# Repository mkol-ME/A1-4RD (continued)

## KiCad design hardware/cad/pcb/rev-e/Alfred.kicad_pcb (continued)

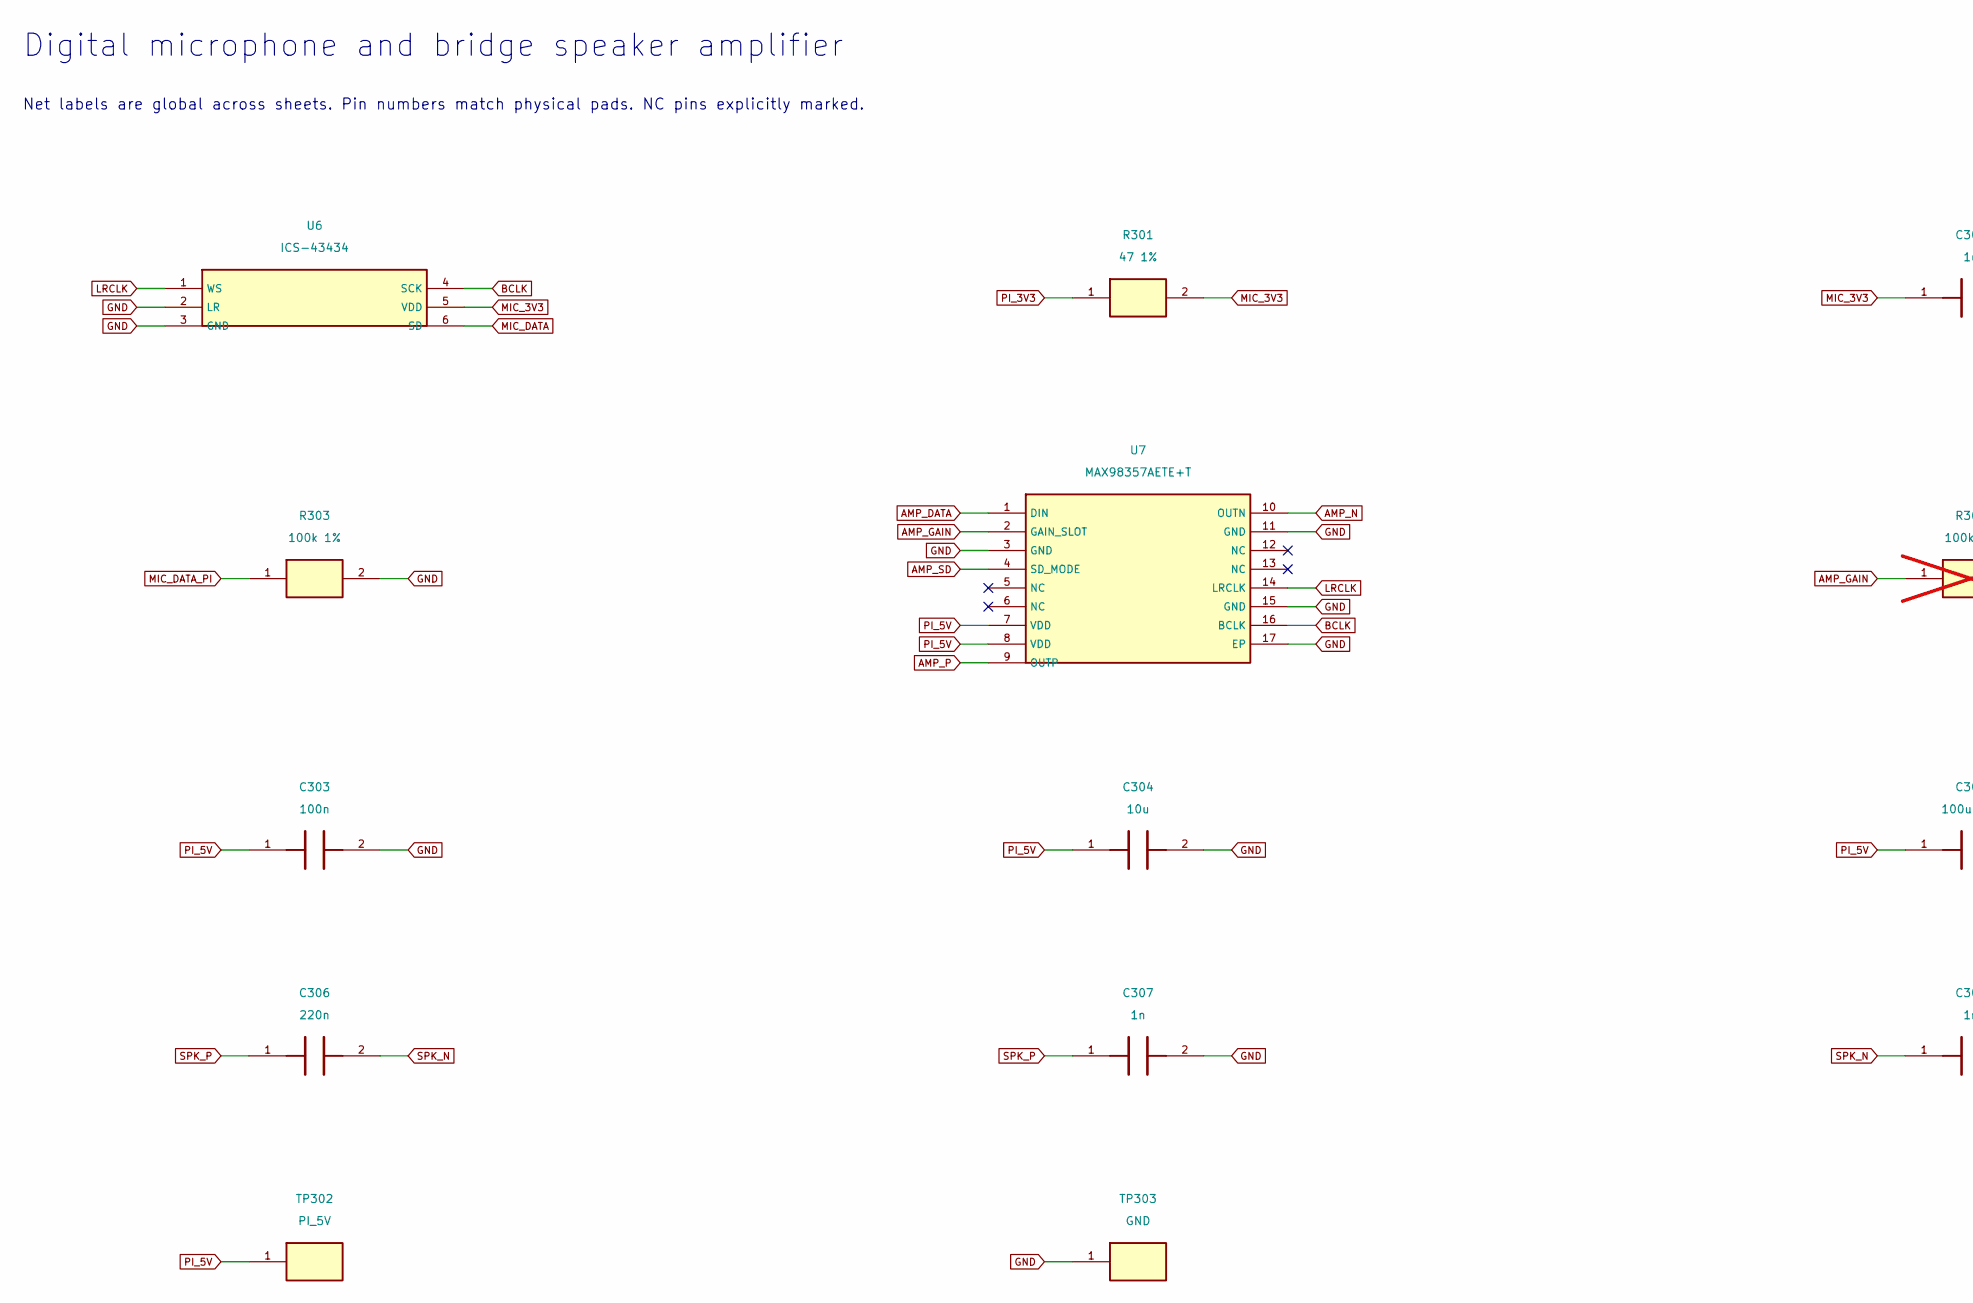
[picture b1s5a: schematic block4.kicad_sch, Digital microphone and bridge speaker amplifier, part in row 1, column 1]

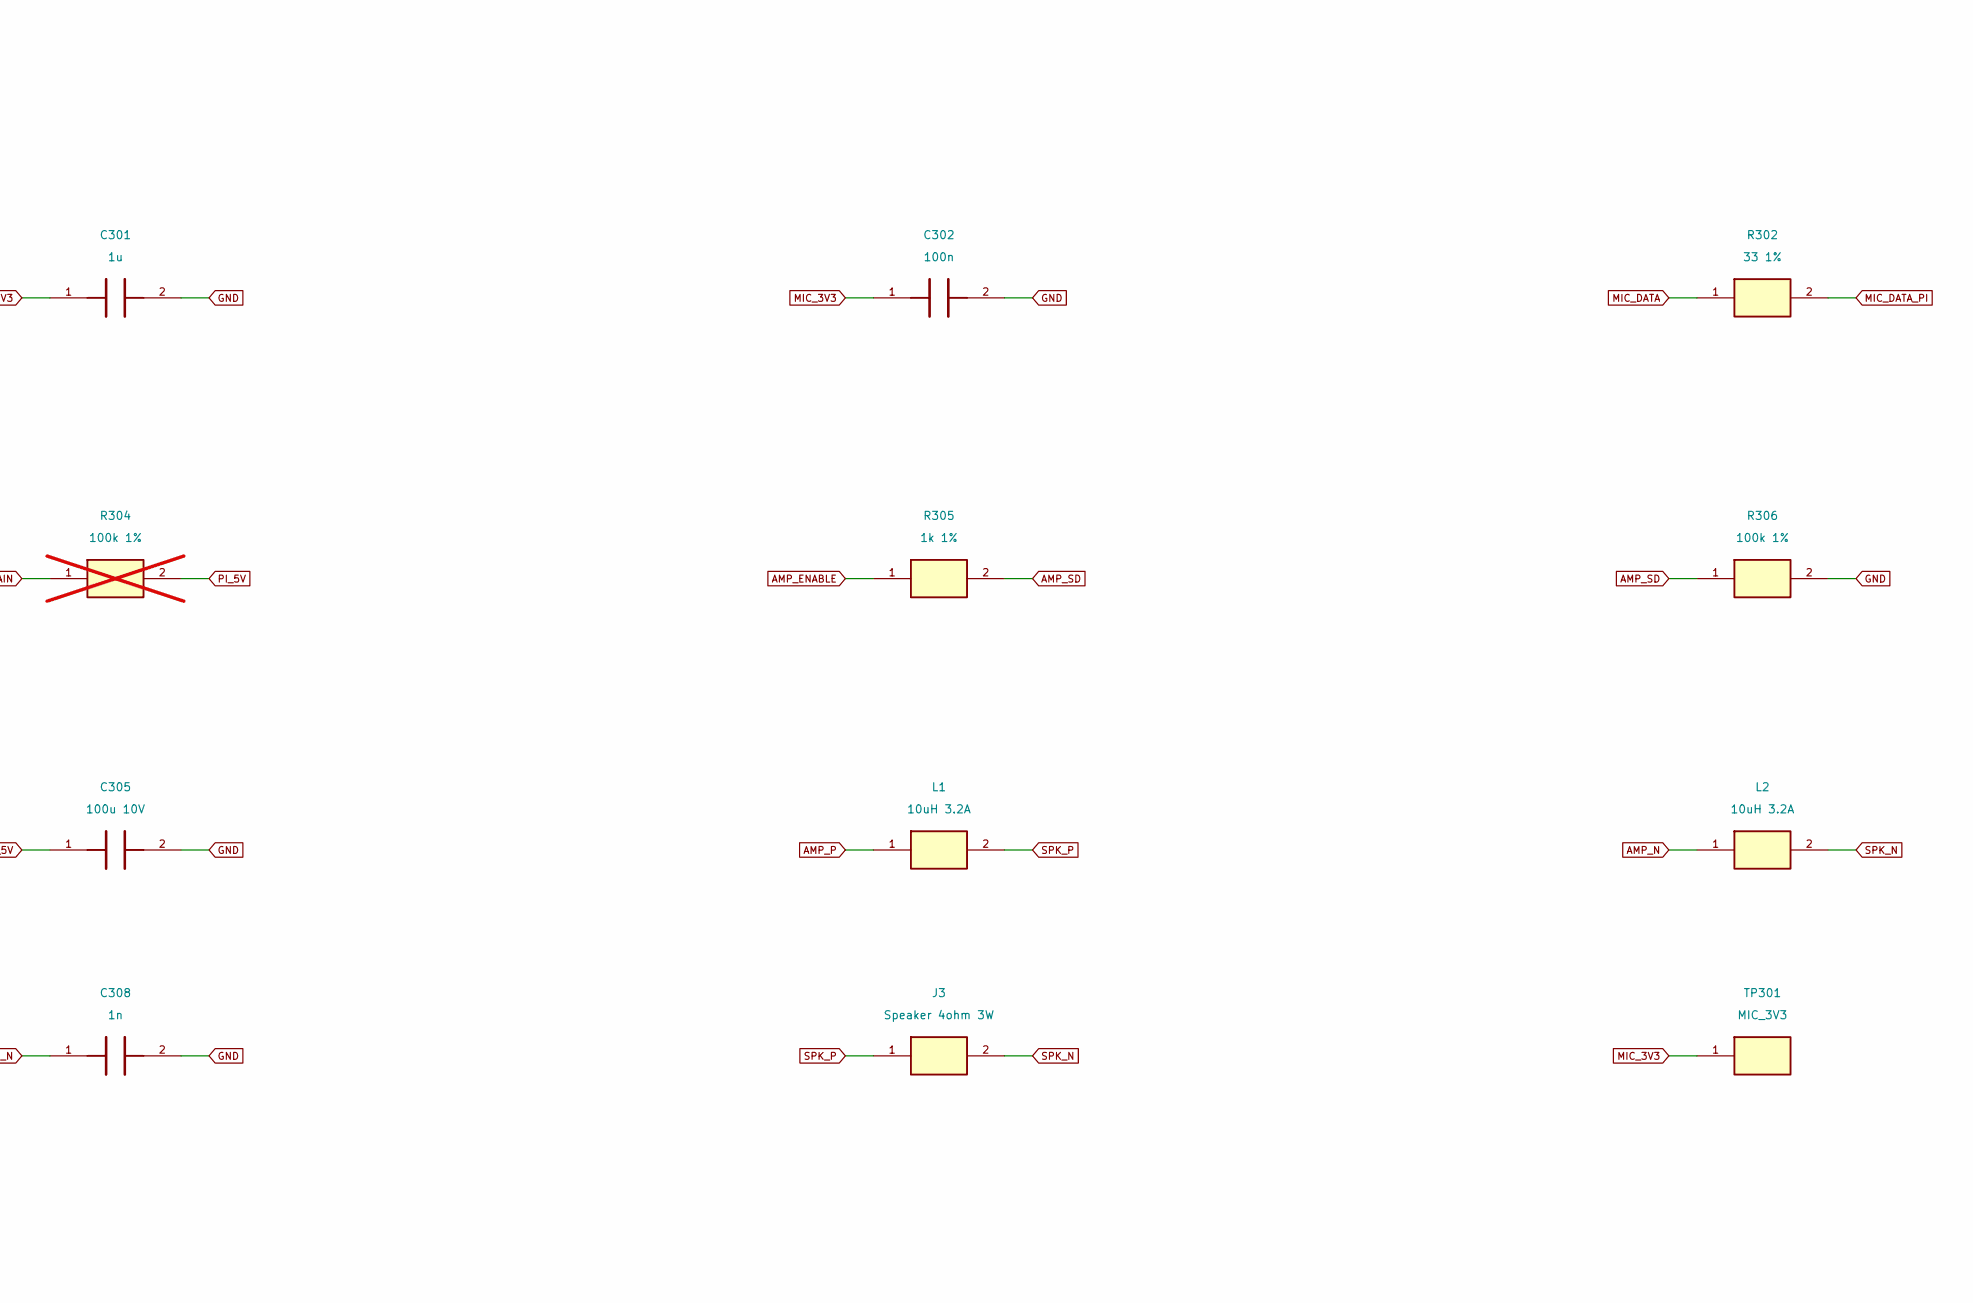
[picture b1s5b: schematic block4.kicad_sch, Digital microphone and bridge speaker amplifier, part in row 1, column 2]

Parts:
C301: 1u; C_0805_2012Metric; MPN C0805C105K5RACTU
C302, C303: 100n; C_0805_2012Metric; MPN C0805C104K5RACTU
C304: 10u; C_1206_3216Metric; MPN C1206C106K4RACTU
C305: 100u 10V; CP_Radial_D5.0mm_P2.00mm; MPN EEU-FR1A101
C306: 220n; C_0805_2012Metric; MPN C0805C224K5RACTU
C307, C308: 1n; C_0805_2012Metric; MPN C0805C102J5GACTU
J3: Speaker 4ohm 3W; TerminalBlock_TE_282834-2_1x02_P2.54mm_Horizontal; MPN 282834-2
L1, L2: 10uH 3.2A; SRN6045TA_100M; MPN SRN6045TA-100M
R301: 47 1%; R_0805_2012Metric; MPN RC0805FR-0747RL
R302: 33 1%; R_0805_2012Metric; MPN RC0805FR-0733RL
R303, R306: 100k 1%; R_0805_2012Metric; MPN RC0805FR-07100KL
R304: 100k 1%; R_0805_DNP_NoPaste; MPN RC0805FR-07100KL; not fitted
R305: 1k 1%; R_0805_2012Metric; MPN RC0805FR-071KL
TP301: MIC_3V3; TestPoint_Pad_D1.5mm; MPN PCB copper test point
TP302: PI_5V; TestPoint_Pad_D1.5mm; MPN PCB copper test point
TP303: GND; TestPoint_Pad_D1.5mm; MPN PCB copper test point
U6: ICS-43434; InvenSense_ICS-43434-6_3.5x2.65mm; MPN ICS-43434
U7: MAX98357AETE+T; TQFN-16-1EP_3x3mm_P0.5mm_EP1.23x1.23mm; MPN MAX98357AETE+T

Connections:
AMP_DATA: U7.1 (DIN); also elsewhere on the board
AMP_ENABLE: R305.1; also elsewhere on the board
AMP_GAIN: R304.1, U7.2 (GAIN_SLOT)
AMP_N: L2.1, U7.10 (OUTN)
AMP_P: L1.1, U7.9 (OUTP)
AMP_SD: R305.2, R306.1, U7.4 (SD_MODE)
BCLK: U6.4 (SCK), U7.16 (BCLK); also elsewhere on the board
GND: C301.2, C302.2, C303.2, C304.2, C305.2, C307.2, C308.2, R303.2, R306.2, TP303.1, U6.2 (LR), U6.3 (GND), U7.3 (GND), U7.11 (GND), U7.15 (GND), U7.17 (EP); also elsewhere on the board
LRCLK: U6.1 (WS), U7.14 (LRCLK); also elsewhere on the board
MIC_3V3: C301.1, C302.1, R301.2, TP301.1, U6.5 (VDD)
MIC_DATA: R302.1, U6.6 (SD)
MIC_DATA_PI: R302.2, R303.1; also elsewhere on the board
PI_3V3: R301.1; also elsewhere on the board
PI_5V: C303.1, C304.1, C305.1, R304.2, TP302.1, U7.7 (VDD), U7.8 (VDD); also elsewhere on the board
SPK_N: C306.2, C308.1, J3.2, L2.2
SPK_P: C306.1, C307.1, J3.1, L1.2

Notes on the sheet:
Digital microphone and bridge speaker amplifier
Net labels are global across sheets. Pin numbers match physical pads. NC pins explicitly marked.

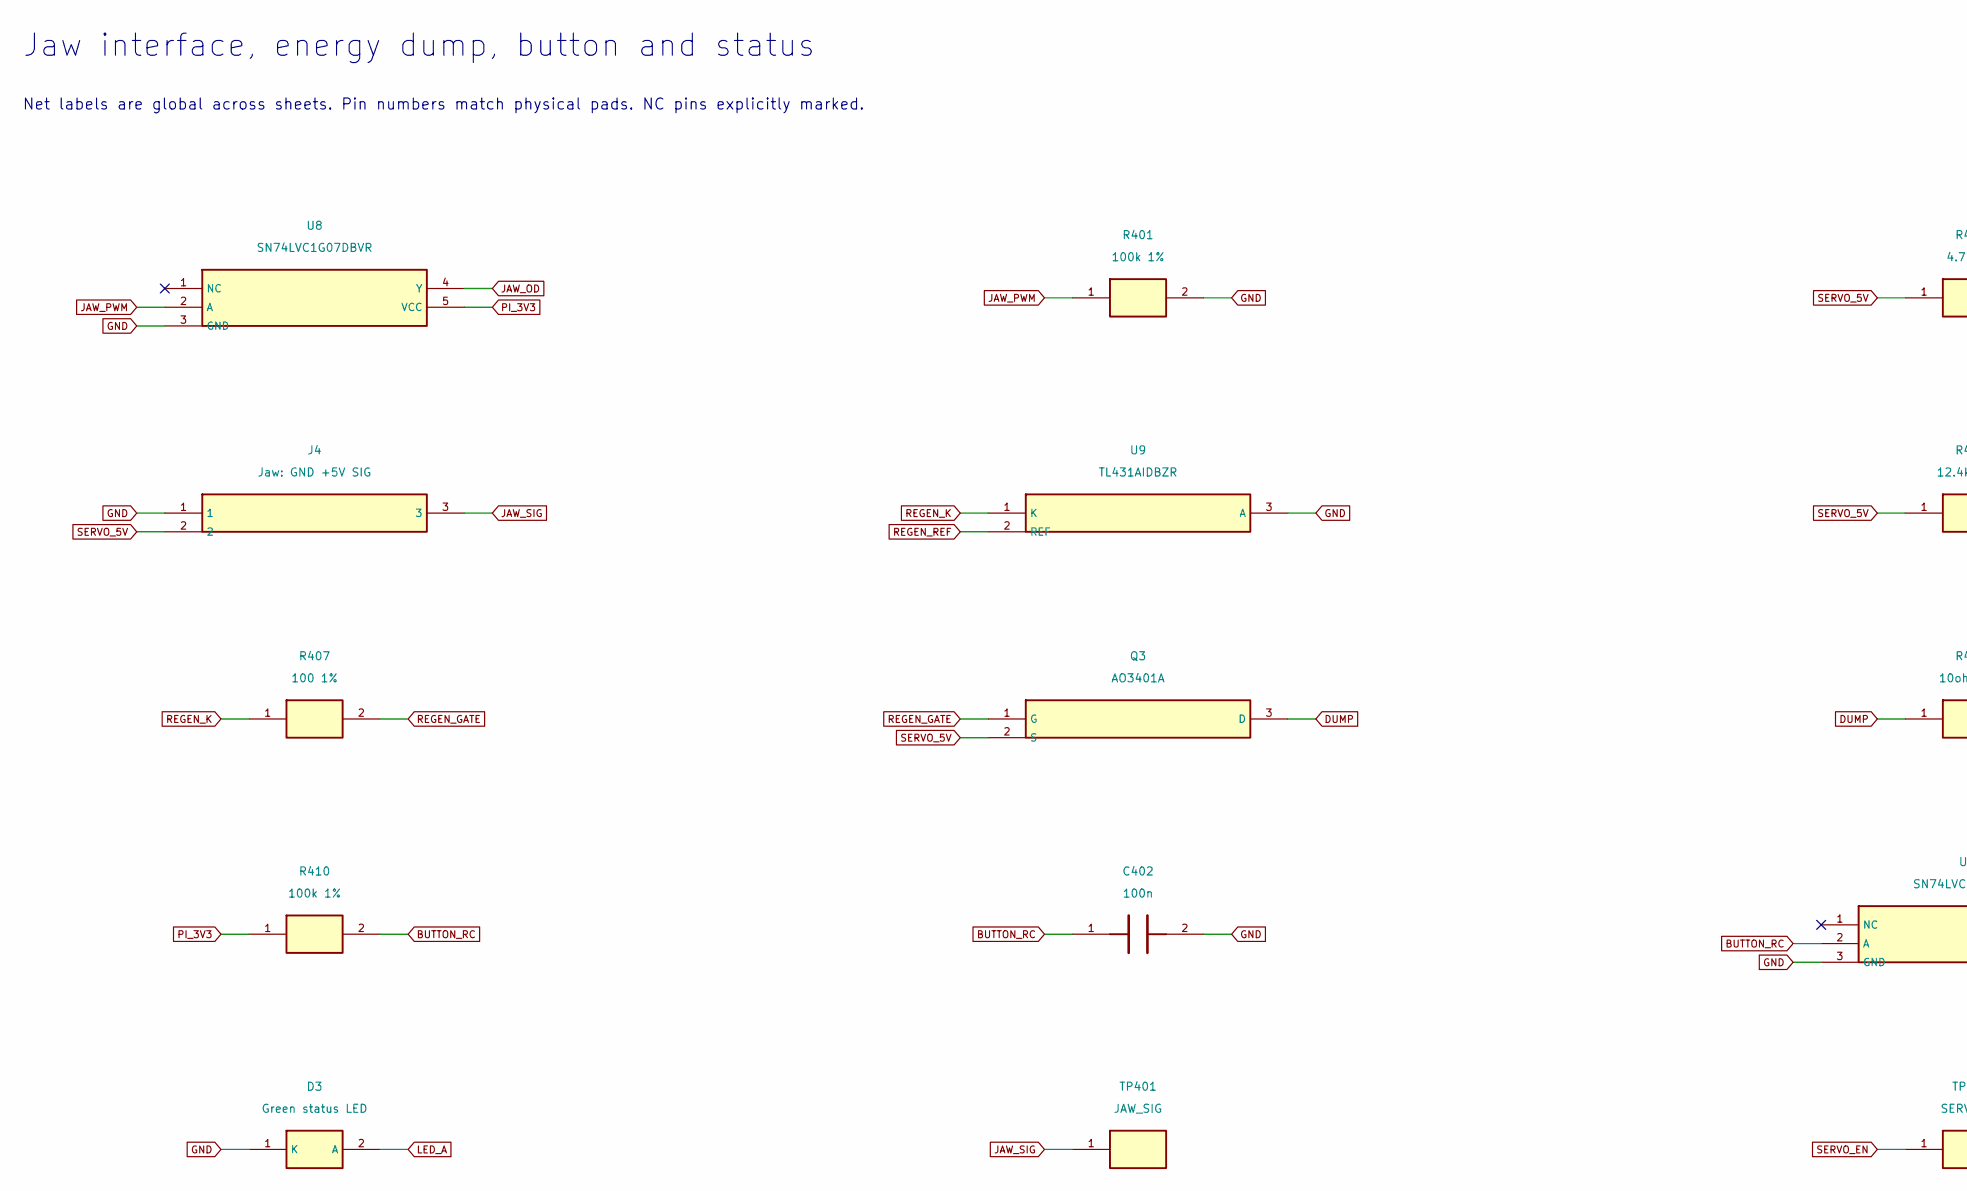
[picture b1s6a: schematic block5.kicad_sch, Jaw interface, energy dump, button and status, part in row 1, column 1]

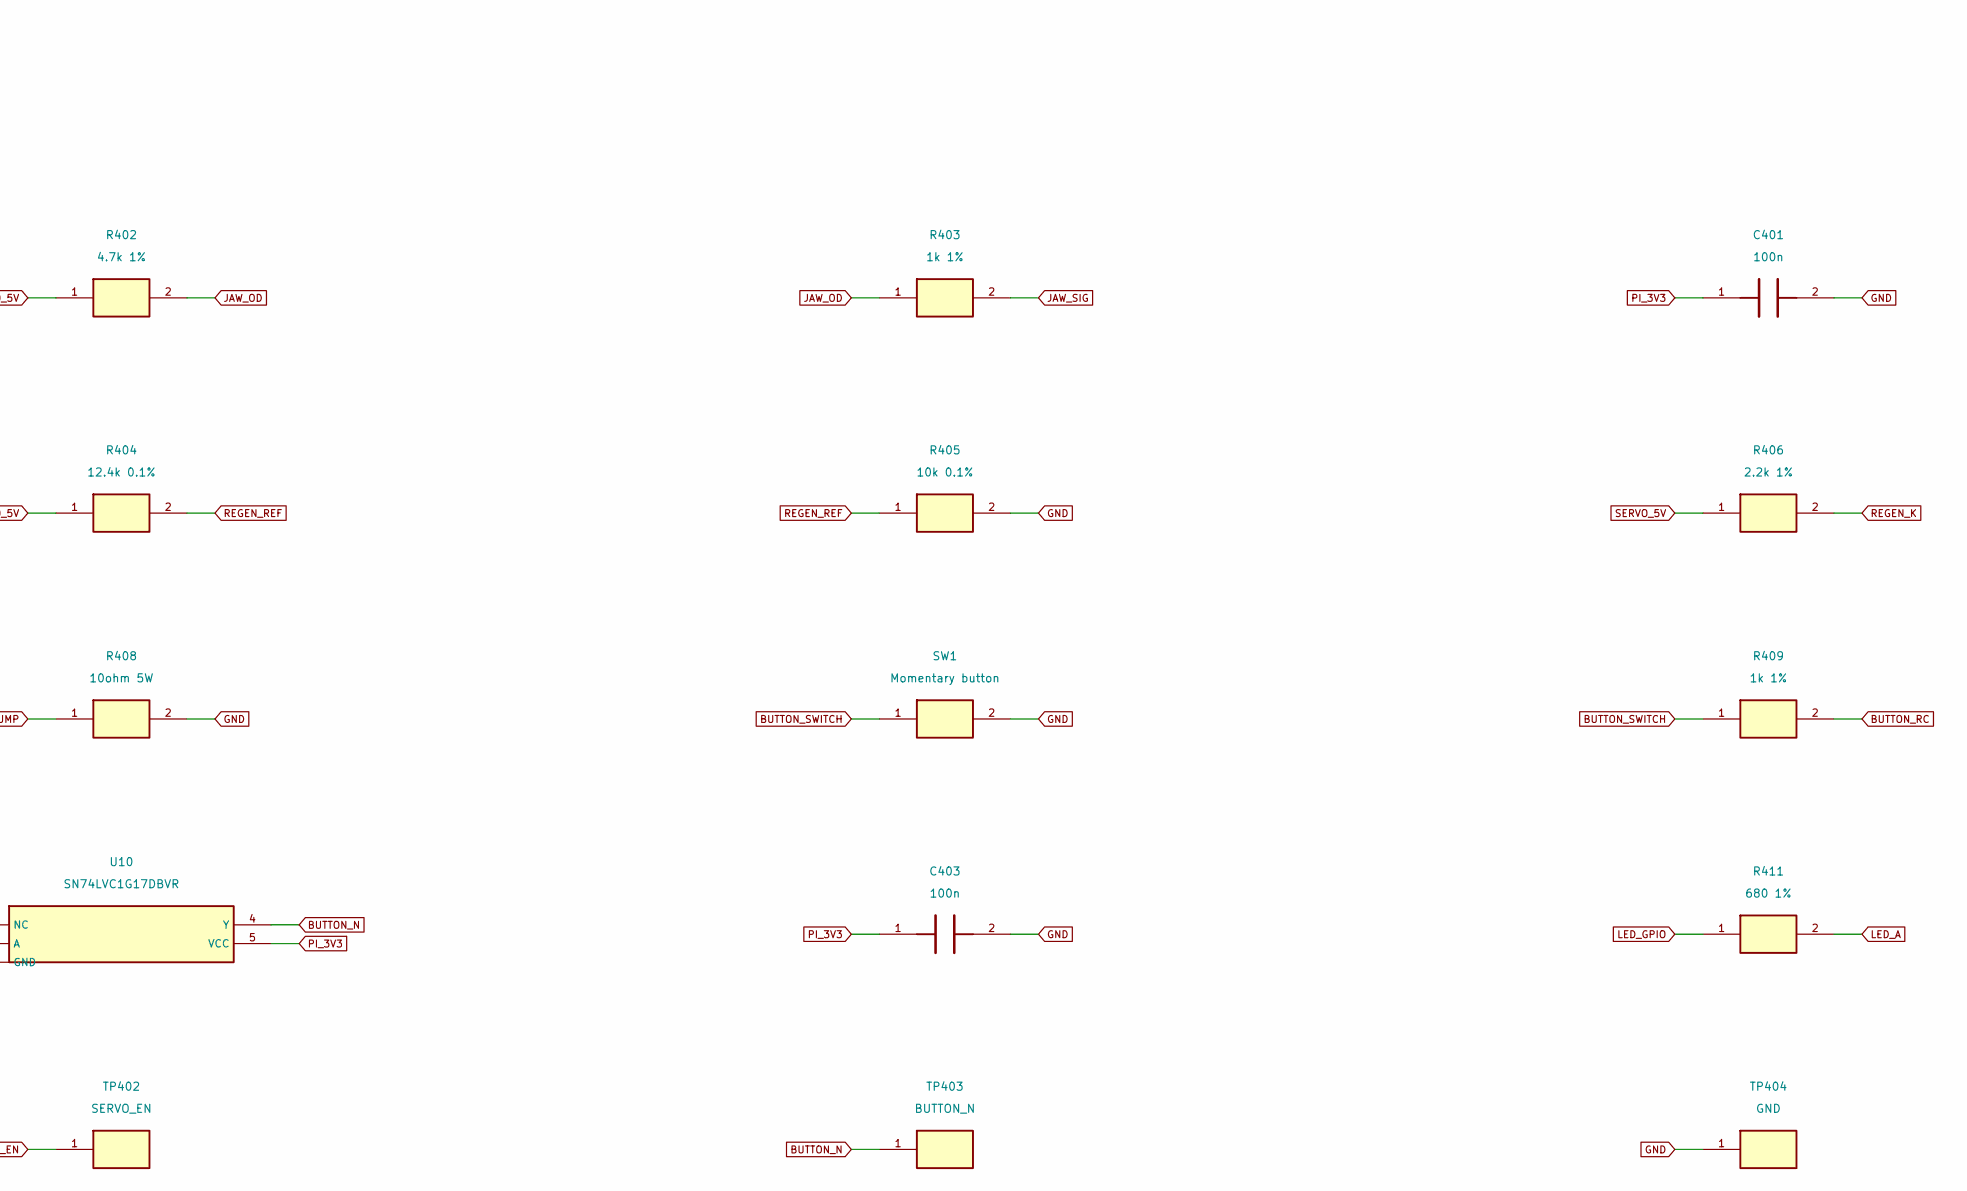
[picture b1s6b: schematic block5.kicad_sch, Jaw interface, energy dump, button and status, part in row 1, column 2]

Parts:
C401, C402, C403: 100n; C_0805_2012Metric; MPN C0805C104K5RACTU
D3: Green status LED; LED_D3.0mm; MPN WP710A10SGC
J4: Jaw: GND +5V SIG; PinHeader_1x03_P2.54mm_Vertical; MPN TSW-103-07-G-S
Q3: AO3401A; SOT-23; MPN AO3401A
R401, R410: 100k 1%; R_0805_2012Metric; MPN RC0805FR-07100KL
R402: 4.7k 1%; R_0805_2012Metric; MPN RC0805FR-074K7L
R403, R409: 1k 1%; R_0805_2012Metric; MPN RC0805FR-071KL
R404: 12.4k 0.1%; R_0805_2012Metric; MPN RT0805BRD0712K4L
R405: 10k 0.1%; R_0805_2012Metric; MPN RT0805BRD0710KL
R406: 2.2k 1%; R_0805_2012Metric; MPN RC0805FR-072K2L
R407: 100 1%; R_0805_2012Metric; MPN RC0805FR-07100RL
R408: 10ohm 5W; R_Axial_Power_L25.0mm_W9.0mm_P30.48mm; MPN SQP500JB-10R
R411: 680 1%; R_0805_2012Metric; MPN RC0805FR-07680RL
SW1: Momentary button; SW_PUSH_6mm_H4.3mm; MPN B3F-1000
TP401: JAW_SIG; TestPoint_Pad_D1.5mm; MPN PCB copper test point
TP402: SERVO_EN; TestPoint_Pad_D1.5mm; MPN PCB copper test point
TP403: BUTTON_N; TestPoint_Pad_D1.5mm; MPN PCB copper test point
TP404: GND; TestPoint_Pad_D1.5mm; MPN PCB copper test point
U8: SN74LVC1G07DBVR; SOT-23-5; MPN SN74LVC1G07DBVR
U9: TL431AIDBZR; SOT-23; MPN TL431AIDBZR
U10: SN74LVC1G17DBVR; SOT-23-5; MPN SN74LVC1G17DBVR

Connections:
BUTTON_N: TP403.1, U10.4 (Y); also elsewhere on the board
BUTTON_RC: C402.1, R409.2, R410.2, U10.2 (A)
BUTTON_SWITCH: R409.1, SW1.1
DUMP: Q3.3 (D), R408.1
GND: C401.2, C402.2, C403.2, D3.1 (K), J4.1, R401.2, R405.2, R408.2, SW1.2, TP404.1, U8.3 (GND), U9.3 (A), U10.3 (GND); also elsewhere on the board
JAW_OD: R402.2, R403.1, U8.4 (Y)
JAW_PWM: R401.1, U8.2 (A); also elsewhere on the board
JAW_SIG: J4.3, R403.2, TP401.1
LED_A: D3.2 (A), R411.2
LED_GPIO: R411.1; also elsewhere on the board
PI_3V3: C401.1, C403.1, R410.1, U8.5 (VCC), U10.5 (VCC); also elsewhere on the board
REGEN_GATE: Q3.1 (G), R407.2
REGEN_K: R406.2, R407.1, U9.1 (K)
REGEN_REF: R404.2, R405.1, U9.2 (REF)
SERVO_5V: J4.2, Q3.2 (S), R402.1, R404.1, R406.1; also elsewhere on the board
SERVO_EN: TP402.1; also elsewhere on the board

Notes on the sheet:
Jaw interface, energy dump, button and status
Net labels are global across sheets. Pin numbers match physical pads. NC pins explicitly marked.

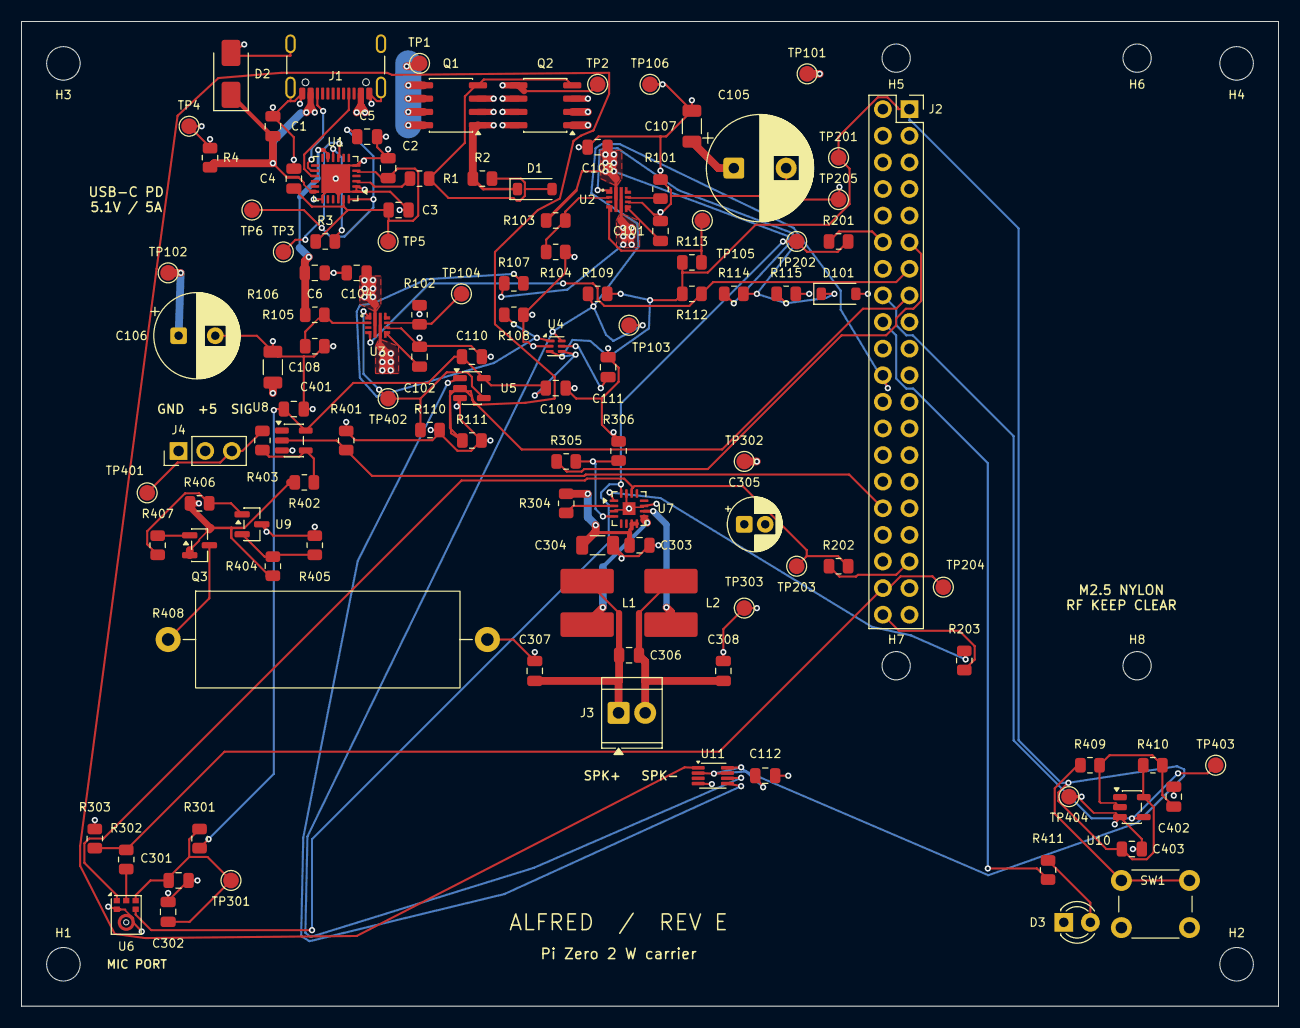
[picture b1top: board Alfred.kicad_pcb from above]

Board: 4 copper layers, 120.0 x 94.0 mm, 125 parts (0 on the bottom side), 58 nets.

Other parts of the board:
H1, H2, H3, H4: MountingHole_3.2mm_M3
H5, H6, H7, H8: MountingHole_2.7mm_M2.5

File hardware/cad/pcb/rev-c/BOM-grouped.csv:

References fitted,Quantity fitted per board,Lean purchase quantity for ONE board,Optional purchase with small-passive spares,MPN,Value,Footprint,Unit USD allowance - NOT QUOTE,Lean extended USD allowance,Price evidence
J3,1,1,1,282834-2,Speaker 4ohm 3W,TerminalBlock_TE-Connectivity:TerminalBlock_TE_282834-2_1x02_P2.54mm_Horizontal,0.8,0.8,Inherited allowance; refresh supplier cart
Q3,1,1,1,AO3401A,AO3401A,Package_TO_SOT_SMD:SOT-23,0.25,0.25,Inherited allowance; refresh supplier cart
SW1,1,1,1,B3F-1000,Momentary button,Button_Switch_THT:SW_PUSH_6mm_H4.3mm,0.3,0.3,Inherited allowance; refresh supplier cart
D1,1,1,1,BZT52C10-7-F,10V gate zener,Diode_SMD:D_SOD-123,0.12,0.12,Inherited allowance; refresh supplier cart
"C111, C307, C308",3,3,5,C0805C102J5GACTU,1n,Capacitor_SMD:C_0805_2012Metric,0.15,0.45,Inherited allowance; refresh supplier cart
"C3, C4, C103, C104, C109, C110, C302, C303, C401, C402, C403",11,11,13,C0805C104K5RACTU,100n,Capacitor_SMD:C_0805_2012Metric,0.15,1.65,Inherited allowance; refresh supplier cart
"C1, C2, C5, C6, C301",5,5,7,C0805C105K5RACTU,1u,Capacitor_SMD:C_0805_2012Metric,0.15,0.75,Inherited allowance; refresh supplier cart
C306,1,1,3,C0805C224K5RACTU,220n,Capacitor_SMD:C_0805_2012Metric,0.15,0.15,Inherited allowance; refresh supplier cart
"C101, C102",2,2,4,C0805C472J5GACTU,4.7n,Capacitor_SMD:C_0805_2012Metric,0.15,0.3,Inherited allowance; refresh supplier cart
"C107, C108, C304",3,3,5,C1206C106K4RACTU,10u,Capacitor_SMD:C_1206_3216Metric,0.15,0.45,Inherited allowance; refresh supplier cart
U1,1,1,1,CYPD3177-24LQXQ,CYPD3177-24LQXQ,Package_DFN_QFN:QFN-24-1EP_4x4mm_P0.5mm_EP2.75x2.75mm,3.5,3.5,Inherited allowance; refresh supplier cart
C305,1,1,1,EEU-FR1A101,100u 10V,Capacitor_THT:CP_Radial_D5.0mm_P2.00mm,0.35,0.35,Inherited allowance; refresh supplier cart
C106,1,1,1,EEU-FR1A102L,1000u 10V,Capacitor_THT:CP_Radial_D8.0mm_P3.50mm,0.85,0.85,Inherited allowance; refresh supplier cart
C105,1,1,1,EEU-FR1A222L,2200u 10V,Capacitor_THT:CP_Radial_D10.0mm_P5.00mm,1.3,1.3,Inherited allowance; refresh supplier cart
"Q1, Q2",2,2,2,FDS6673BZ,FDS6673BZ,Package_SO:SO-8_3.9x4.9mm_P1.27mm,1.76,3.52,"DigiKey indexed substitute listing: $1.76, 4781 in stock, checked 2026-09-10; not reserved"
U6,1,1,1,ICS-43434,ICS-43434,Sensor_Audio:InvenSense_ICS-43434-6_3.5x2.65mm,4.2,4.2,Inherited allowance; refresh supplier cart
U7,1,1,1,MAX98357AETE+T,MAX98357AETE+T,Package_DFN_QFN:TQFN-16-1EP_3x3mm_P0.5mm_EP1.23x1.23mm,4.08,4.08,Inherited allowance; refresh supplier cart
D101,1,1,1,MMSZ5V1T1G,5.1V EN clamp,Diode_SMD:D_SOD-123,0.17,0.17,"DigiKey indexed substitute listing: $0.17, 101196 in stock, checked 2026-09-10; not reserved"
"R2, R110, R111, R303, R306, R401, R410",7,7,9,RC0805FR-07100KL,100k 1%,Resistor_SMD:R_0805_2012Metric,0.05,0.35,Inherited allowance; refresh supplier cart
R407,1,1,3,RC0805FR-07100RL,100 1%,Resistor_SMD:R_0805_2012Metric,0.05,0.05,Inherited allowance; refresh supplier cart
"R4, R112, R113, R114, R115",5,5,7,RC0805FR-0710KL,10k 1%,Resistor_SMD:R_0805_2012Metric,0.05,0.25,Inherited allowance; refresh supplier cart
"R1, R305, R403, R409",4,4,6,RC0805FR-071KL,1k 1%,Resistor_SMD:R_0805_2012Metric,0.05,0.2,Inherited allowance; refresh supplier cart
R406,1,1,3,RC0805FR-072K2L,2.2k 1%,Resistor_SMD:R_0805_2012Metric,0.05,0.05,Inherited allowance; refresh supplier cart
R109,1,1,3,RC0805FR-072M2L,2.2M 1%,Resistor_SMD:R_0805_2012Metric,0.05,0.05,Inherited allowance; refresh supplier cart
"R201, R202, R203, R302",4,4,6,RC0805FR-0733RL,33 1%,Resistor_SMD:R_0805_2012Metric,0.05,0.2,Inherited allowance; refresh supplier cart
R301,1,1,3,RC0805FR-0747RL,47 1%,Resistor_SMD:R_0805_2012Metric,0.05,0.05,Inherited allowance; refresh supplier cart
R3,1,1,3,RC0805FR-0749K9L,49.9k 1%,Resistor_SMD:R_0805_2012Metric,0.05,0.05,Inherited allowance; refresh supplier cart
R402,1,1,3,RC0805FR-074K7L,4.7k 1%,Resistor_SMD:R_0805_2012Metric,0.05,0.05,Inherited allowance; refresh supplier cart
R411,1,1,3,RC0805FR-07680RL,680 1%,Resistor_SMD:R_0805_2012Metric,0.05,0.05,Inherited allowance; refresh supplier cart
"R104, R106, R108, R405",4,4,6,RT0805BRD0710KL,10k 0.1%,Resistor_SMD:R_0805_2012Metric,0.18,0.72,Inherited allowance; refresh supplier cart
R404,1,1,3,RT0805BRD0712K4L,12.4k 0.1%,Resistor_SMD:R_0805_2012Metric,0.18,0.18,Inherited allowance; refresh supplier cart
R101,1,1,3,RT0805BRD071KL,1k 0.1%,Resistor_SMD:R_0805_2012Metric,0.18,0.18,Inherited allowance; refresh supplier cart
R107,1,1,3,RT0805BRD0729K8L,29.8k 0.1%,Resistor_SMD:R_0805_2012Metric,0.18,0.18,Inherited allowance; refresh supplier cart
"R103, R105",2,2,4,RT0805BRD0734KL,34.0k 0.1%,Resistor_SMD:R_0805_2012Metric,0.18,0.36,Inherited allowance; refresh supplier cart
R102,1,1,3,RT0805BRD073K32L,3.32k 0.1%,Resistor_SMD:R_0805_2012Metric,0.18,0.18,Inherited allowance; refresh supplier cart
D2,1,1,1,SMAJ15A-13-F,15V transient suppressor,Diode_SMD:D_SMA,0.45,0.45,Inherited allowance; refresh supplier cart
U8,1,1,1,SN74LVC1G07DBVR,SN74LVC1G07DBVR,Package_TO_SOT_SMD:SOT-23-5,0.35,0.35,Inherited allowance; refresh supplier cart
U5,1,1,1,SN74LVC1G08DBVR,SN74LVC1G08DBVR,Package_TO_SOT_SMD:SOT-23-5,0.35,0.35,Inherited allowance; refresh supplier cart
U10,1,1,1,SN74LVC1G17DBVR,SN74LVC1G17DBVR,Package_TO_SOT_SMD:SOT-23-5,0.4,0.4,Inherited allowance; refresh supplier cart
R408,1,1,1,SQP500JB-10R,10ohm 5W,Resistor_THT:R_Axial_Power_L25.0mm_W9.0mm_P30.48mm,0.6,0.6,Inherited allowance; refresh supplier cart
"L1, L2",2,2,2,SRN6045TA-100M,10uH 3.2A,Alfred:SRN6045TA_100M,0.75,1.5,Inherited allowance; refresh supplier cart
J2,1,1,1,SSW-120-01-G-D,Pi Zero 2 W carrier socket,Connector_PinSocket_2.54mm:PinSocket_2x20_P2.54mm_Vertical,4.5,4.5,Inherited allowance; refresh supplier cart
U9,1,1,1,TL431AIDBZR,TL431AIDBZR,Package_TO_SOT_SMD:SOT-23,0.4,0.4,Inherited allowance; refresh supplier cart
U4,1,1,1,TLV3012BIDBVR,TLV3012BIDBVR,Package_TO_SOT_SMD:SOT-23-6,2.78,2.78,Inherited allowance; refresh supplier cart
"U2, U3",2,2,2,TPS259470LRPWR,TPS259470LRPWR,Alfred:TI_RPW0010A,1.72,3.44,Inherited allowance; refresh supplier cart
J4,1,1,1,TSW-103-07-G-S,Jaw: GND +5V SIG,Connector_PinHeader_2.54mm:PinHeader_1x03_P2.54mm_Vertical,0.45,0.45,Inherited allowance; refresh supplier cart
J1,1,1,1,USB4105-GF-A,USB-C 5V/5A PD,Connector_USB:USB_C_Receptacle_GCT_USB4105-xx-A_16P_TopMnt_Horizontal,1.2,1.2,Inherited allowance; refresh supplier cart
D3,1,1,1,WP710A10SGC,Green status LED,LED_THT:LED_D3.0mm,0.3,0.3,Inherited allowance; refresh supplier cart

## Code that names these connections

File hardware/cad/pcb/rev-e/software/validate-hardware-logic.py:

from pathlib import Path
from itertools import product
import json
O=Path(__file__).resolve().parent.parent;by={a['ref']:a for a in json.loads((O/'design-data.json').read_text())}
assert by['U4']['pins']=={'1':'UV_SENSE','2':'GND','3':'PI_3V3','4':'PI_3V3','5':'UV_DELAY','6':'SUPPLY_OK'}
assert by['U11']['pins']=={'1':'SERVO_REQUEST','2':'PI_3V3','3':None,'4':'GND','5':'SERVO_ARMED','6':'SUPPLY_OK','7':'PI_3V3','8':'PI_3V3'}
assert by['U5']['pins']['1']=='SERVO_ARMED' and by['U5']['pins']['2']=='SERVO_REQUEST'
# Exhaust all eight-event binary request/supply-good sequences; start with reset asserted.
count=0
for events in product(product([False,True],repeat=2),repeat=8):
 q=False;prev=False;last_fault=True;armed_since_fault=False
 for req,good in events:
  rise=req and not prev
  if not good:q=False;armed_since_fault=False
  elif rise:q=True;armed_since_fault=True
  en=q and req
  assert not en or (good and armed_since_fault)
  if not req:assert not en
  if last_fault and good and req and prev:assert not en
  prev=req;last_fault=not good
 count+=1
print('Latch sequences:',count,'PASS (truth-table model, not analog simulation)')
# Datasheet +/-1% positive and negative thresholds, divider +/-0.1%, sense leakage +/-100 nA conservatively.
def limit(th,sgn):
 rt=32100*(1+sgn*.001);rb=10000*(1-sgn*.001)
 return th*(1+sgn*.01)*(1+rt/rb)+sgn*100e-9*rt
vals={'fall_nom':1.15*4.21,'fall_min':limit(1.15,-1),'fall_max':limit(1.15,1),'rise_nom':1.157*4.21,'rise_min':limit(1.157,-1),'rise_max':limit(1.157,1),'rail_25C_servo_off':5.1-2.85*(.0164+.0283),'rail_25C_allocation':5.1-4.1*.0164-2.85*.0283}
print(json.dumps(vals,indent=2))
